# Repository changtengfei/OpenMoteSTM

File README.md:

View this project on [CADLAB.io](https://cadlab.io/project/1063). 

OpenSource Hardware of OpenMoteSTM
====================================================

Hello, here is the source of OpenMoteSTM board, including device library, schematic and PCB. All of those are designed by eagle. We also provide a 3d model for openmotestm using sketchUp!!! You can open the openmotestm.skp file with sketchUp to see what openmotestm looks like. Part of package/device/model came from the library of eagle and sparkfun. 

Using OpenMoteSTM with OpenWSN
====================================================

Hardware & Tools
----------------------------------------------------

* OpenMoteSTM Motes         Please Contact: tengfei.chang@gmail.com
* Micro-B USB Cables        You can buy them online anywhere, or maybe you already have one :)
* Jlink Debugger            https://www.segger.com/jlink-debug-probes.html
* Jlink adapter             https://www.segger.com/jlink-adapters-9pin-cortexm.html

Software Installation
----------------------------------------------------

* IAR Embedded Workbench for ARM : Version 6.60     http://www.iar.com
* python 2.7:               http://python.org/download/
* PySerial 2.6:             http://pyserial.sourceforge.net/
* PyDispatcher 2.0.3:       http://pydispatcher.sourceforge.net/
* PyWin32:                  https://sourceforge.net/projects/pywin32/files/pywin32/
* SCons:                    http://scons.org/download.php
* Tap for Windows:          http://openvpn.net/index.php/download/community-downloads.html
* Silicon Labs CP2102:      http://www.silabs.com/support/pages/document-library.aspx?p=Interface&f=USB%20Bridges&pn=CP2102

Installation of Tap
----------------------------------------------------
1. install tun
2. configure tun
    * Go: "Start"->"Programs"->Tap For Windows->utilities->"Add a new TAP virtual ethernet adapter" 
    * Open Network Adapter，Looking for "Local Area Connection" adapter which is created by Tap windows
    * Rename it by "OpenWSN"
    * Enter following code in a windows command prompt， setting IP：
    
            netsh interface ipv4 add address name=OpenWSN address=10.2.0.1 mask=255.255.0.0
            netsh interface ipv6 add address interface=OpenWSN address=bbbb::1/64   
    
    * Enable Routing ("IEEE802.3" is the network interface you are using to connect to internet)

            netsh interface ipv4 set interface interface=IEEE802.3 forwarding=enabled
            netsh interface ipv4 set interface interface=OpenWSN forwarding=enabled

            netsh interface ipv6 set interface interface=IEEE802.3 forwarding=enabled
            netsh interface ipv6 set interface interface=OpenWSN forwarding=enabled
    
    * Add path to routing table

            netsh interface ipv6 delete route bbbb::/64 OpenWSN
            netsh interface ipv6 add    route bbbb::/64 OpenWSN fe80::8

Source Code
-----------------------------------------------------
* openwsn-sw:               https://codeload.github.com/openwsn-berkeley/openwsn-sw/zip/REL-1.8.0
* openwsn-fw:               https://codeload.github.com/openwsn-berkeley/openwsn-fw/zip/REL-1.8.0
* coap:                     https://codeload.github.com/openwsn-berkeley/coap/zip/develop

-All extracted folders need to be place at same level-

Downloading led_blink Program
-----------------------------------------------------
1. Open "IAR for ARM"
2. GO: File->Open->Workspace
3. choosing "openmotestm.eww"
    * the file is at : openwsn-fw-REL-1.8.0\projects\openmotestm directory
4. All the projects will shown on the Workspace(left of the GUI)，right click to select "01bsp_leds-Debug" project, then choose "Set as Active" in the prompt menu.    
5. Downloading and Debugging by left clicking the "Green Triangle Button",
    * tips: "Ctrl + D" is the short-cut of this functions
6. After downloading，IAR will stop at debugging mode. Press F5 to start the program. You will see the LEDs will blink by sequence

Using OpenWSN Program
-----------------------------------------------------
1. Downloading "03oos_openwsn-Debug" program by the procedures above
2. Connect OpenMoteSTM to PC by USB Cabel，PC will install the Silicon driver for OpenMoteSTM
3. Open a windows prompt, and enter the following code to start openvisualizer
        cd "Your\openwsn-sw_REL-1.8.0\Directory"\software\openvisualizer\
        scons runweb
3. Open your favourite brower and type in "localhost:8080" or "127.0.0.1:8080", You will see the openwsn openvisualizer page.
4. click "toggle" button to set the mote as DAGROOT. If everything goes well, you will find the blue LED light and the green one blinks. To see what's going behind them, please visit: http://openwsn.org

Contact & Help
-----------------------------------------------------
If you have any questions, please don't hesitate to contact tengfei.chang@gmail.com

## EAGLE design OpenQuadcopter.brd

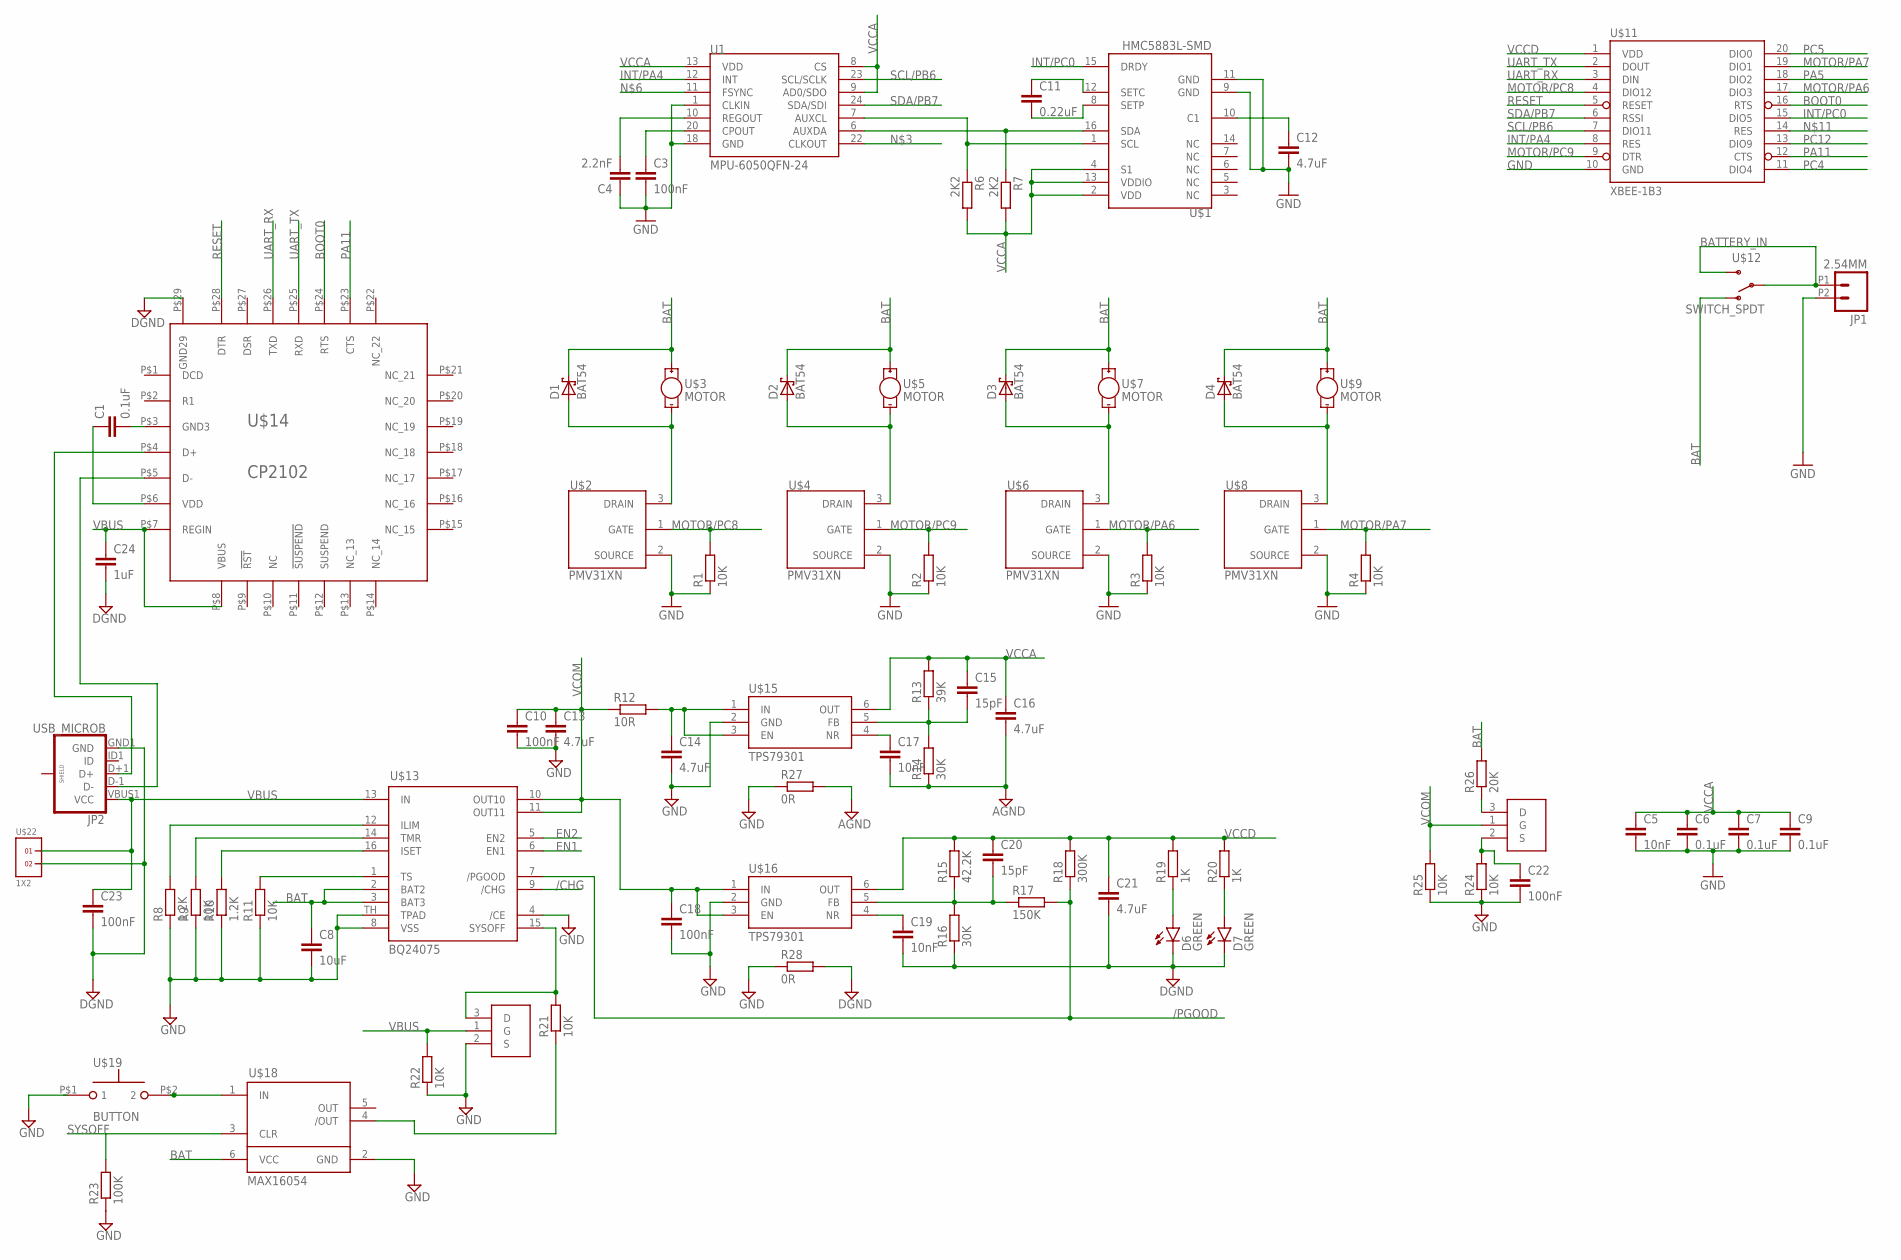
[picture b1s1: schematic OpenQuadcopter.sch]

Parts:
C1, C6, C7, C9: 0.1uF; C0402
C3, C10, C18, C22, C23: 100nF; C0402
C4: 2.2nF; C0402
C5, C17, C19: 10nF; C0402
C8: 10uF; C0603
C11: 0.22uF; C0402
C12, C13, C14, C16, C21: 4.7uF; C0603
C15, C20: 15pF; C0402
C24: 1uF; C0603
D1, D2, D3, D4: BAT54; SOT23
D6, D7: GREEN; LED-0603
JP1: 2.54MM; 1X02_2.54_SCREWTERM
JP2: USB_MICROB; USB-B-MICRO-SMD_V03
R1, R2, R3, R4, R9, R11, R21, R22, R24, R25: 10K; R0402
R6, R7: 2K2; R0402
R8, R10: 1.2K; R0402
R12: 10R; R0402
R13: 39K; R0402
R14, R16: 30K; R0402
R15: 42.2K; R0402
R17: 150K; R0402
R18: 300K; R0402
R19, R20: 1K; R0402
R23: 100K; R0402
R26: 20K; R0402
R27, R28: 0R; R0402
U1: MPU-6050QFN-24; QFN-24-TESTING
U$1: HMC5883L-SMD; 16LPCC
U$2, U$4, U$6, U$8: PMV31XN; SOT23-W
U$3, U$5, U$7, U$9: MOTOR; VIBE-MOTOR-10MM
U$11: XBEE-1B3; XBEE-SMD
U$12: SWITCH_SPDT; KPS-1290
U$13: BQ24075; QFN16
U$14: CP2102; QFN28-5X5
U$15, U$16: TPS79301; SOT23-6
U$17, U$20: 2N7002; SOT23-3
U$18: MAX16054; SOT23-6
U$19: BUTTON
U$22: 1X2

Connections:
/CHG: U$13.9 (/CHG)
/PGOOD: R17.2, R18.1, U$13.7 (/PGOOD)
AGND: C16.2, C17.2, R14.1, R27.2
BAT: C8.1, D1.3 (C), D2.3 (C), D3.3 (C), D4.3 (C), R26.2, U$3.+, U$5.+, U$7.+, U$9.+, U$12.O, U$13.2 (BAT2), U$13.3 (BAT3), U$18.6 (VCC)
BATTERY_IN: JP1.P1 (1), U$12.P, U$12.S
BOOT0: U$11.16 (RTS), U$14.P$24 (RTS)
DGND: C19.2, C21.2, C23.2, C24.2, D6.C, D7.C, JP2.GND1 (GND), R16.1, R28.2, U$14.P$29 (GND29), U$22.2
EN1: U$13.6 (EN1)
EN2: U$13.5 (EN2)
GND: C3.2, C4.1, C5.2, C6.2, C7.2, C8.2, C9.2, C10.2, C12.2, C13.2, C14.2, C18.2, C22.2, JP1.P2 (2), R1.1, R2.1, R3.1, R4.1, R8.1, R9.1, R10.1, R11.1, R22.1, R23.1, R24.1, R25.1, R27.1, R28.1, U1.1 (CLKIN), U1.18 (GND), U$1.9 (GND), U$1.11 (GND), U$2.2 (SOURCE), U$4.2 (SOURCE), U$6.2 (SOURCE), U$8.2 (SOURCE), U$11.10 (GND), U$13.4 (/CE), U$13.8 (VSS), U$13.TH (TPAD), U$15.2 (GND), U$16.2 (GND), U$17.2 (S), U$18.2 (GND)
INT/PA4: U1.12 (INT), U$11.8 (RES)
INT/PC0: U$1.15 (DRDY), U$11.15 (DIO5)
MOTOR/PA6: R3.2, U$6.1 (GATE), U$11.17 (DIO3)
MOTOR/PA7: R4.2, U$8.1 (GATE), U$11.19 (DIO1)
MOTOR/PC8: R1.2, U$2.1 (GATE), U$11.4 (DIO12)
MOTOR/PC9: R2.2, U$4.1 (GATE), U$11.9 (DTR)
unnamed: D2.1 (A), U$4.3 (DRAIN), U$5.-
unnamed: D1.1 (A), U$2.3 (DRAIN), U$3.-
unnamed: R6.1, U1.7 (AUXCL), U$1.1 (SCL)
unnamed: D3.1 (A), U$6.3 (DRAIN), U$7.-
unnamed: D4.1 (A), U$8.3 (DRAIN), U$9.-
unnamed: R7.1, U1.6 (AUXDA), U$1.16 (SDA)
unnamed: C4.2, U1.10 (REGOUT)
unnamed: C1.2, U$14.P$3 (GND3)
unnamed: C3.1, U1.20 (CPOUT)
unnamed: C11.1, U$1.12 (SETC)
unnamed: C11.2, U$1.8 (SETP)
unnamed: R21.1, U$18.4 (/OUT)
unnamed: C12.1, U$1.10 (C1)
unnamed: C1.1, U$14.P$6 (VDD)
unnamed: R8.2, U$13.12 (ILIM)
unnamed: R9.2, U$13.14 (TMR)
unnamed: R10.2, U$13.16 (ISET)
unnamed: R11.2, U$13.1 (TS)
unnamed: R21.2, U$13.15 (SYSOFF), U$17.3 (D)
unnamed: C14.1, R12.2, U$15.1 (IN), U$15.3 (EN)
unnamed: U$18.1 (IN), U$19.P$2 (2)
unnamed: C15.2, R13.1, R14.2, U$15.5 (FB)
unnamed: C17.1, U$15.4 (NR)
unnamed: C19.1, U$16.4 (NR)
unnamed: C20.2, R15.1, R16.2, R17.1, U$16.5 (FB)
unnamed: C22.1, R24.2, U$20.2 (S)
unnamed: D6.A, R19.1
unnamed: D7.A, R20.1
unnamed: R26.1, U$20.3 (D)
unnamed: JP2.D+1 (D+), U$14.P$4 (D+)
unnamed: JP2.D-1 (D-), U$14.P$5 (D-)
PA5: U$11.18 (DIO2)
PA11: U$11.12 (CTS), U$14.P$23 (CTS)
PC4: U$11.11 (DIO4)
PC5: U$11.20 (DIO0)
PC12: U$11.13 (DIO9)
RESET: U$11.5 (RESET), U$14.P$28 (DTR)
SCL/PB6: U1.23 (SCL/SCLK), U$11.7 (DIO11)
SDA/PB7: U1.24 (SDA/SDI), U$11.6 (RSSI)
SYSOFF: R23.2, U$18.3 (CLR)
UART_RX: U$11.3 (DIN), U$14.P$26 (TXD)
UART_TX: U$11.2 (DOUT), U$14.P$25 (RXD)
VBUS: C23.1, C24.1, JP2.VBUS1 (VCC), R22.2, U$13.13 (IN), U$14.P$7 (REGIN), U$14.P$8 (VBUS), U$17.1 (G), U$22.1
VCCA: C5.1, C6.1, C7.1, C9.1, C15.1, C16.1, R6.2, R7.2, R13.2, U1.8 (CS), U1.9 (AD0/SDO), U1.13 (VDD), U$1.2 (VDD), U$1.4 (S1), U$1.13 (VDDIO), U$15.6 (OUT)
VCCD: C20.1, C21.1, R15.2, R18.2, R19.2, R20.2, U$11.1 (VDD), U$16.6 (OUT)
VCOM: C10.1, C13.1, C18.1, R12.1, R25.2, U$13.10 (OUT10), U$13.11 (OUT11), U$16.1 (IN), U$16.3 (EN), U$20.1 (G)

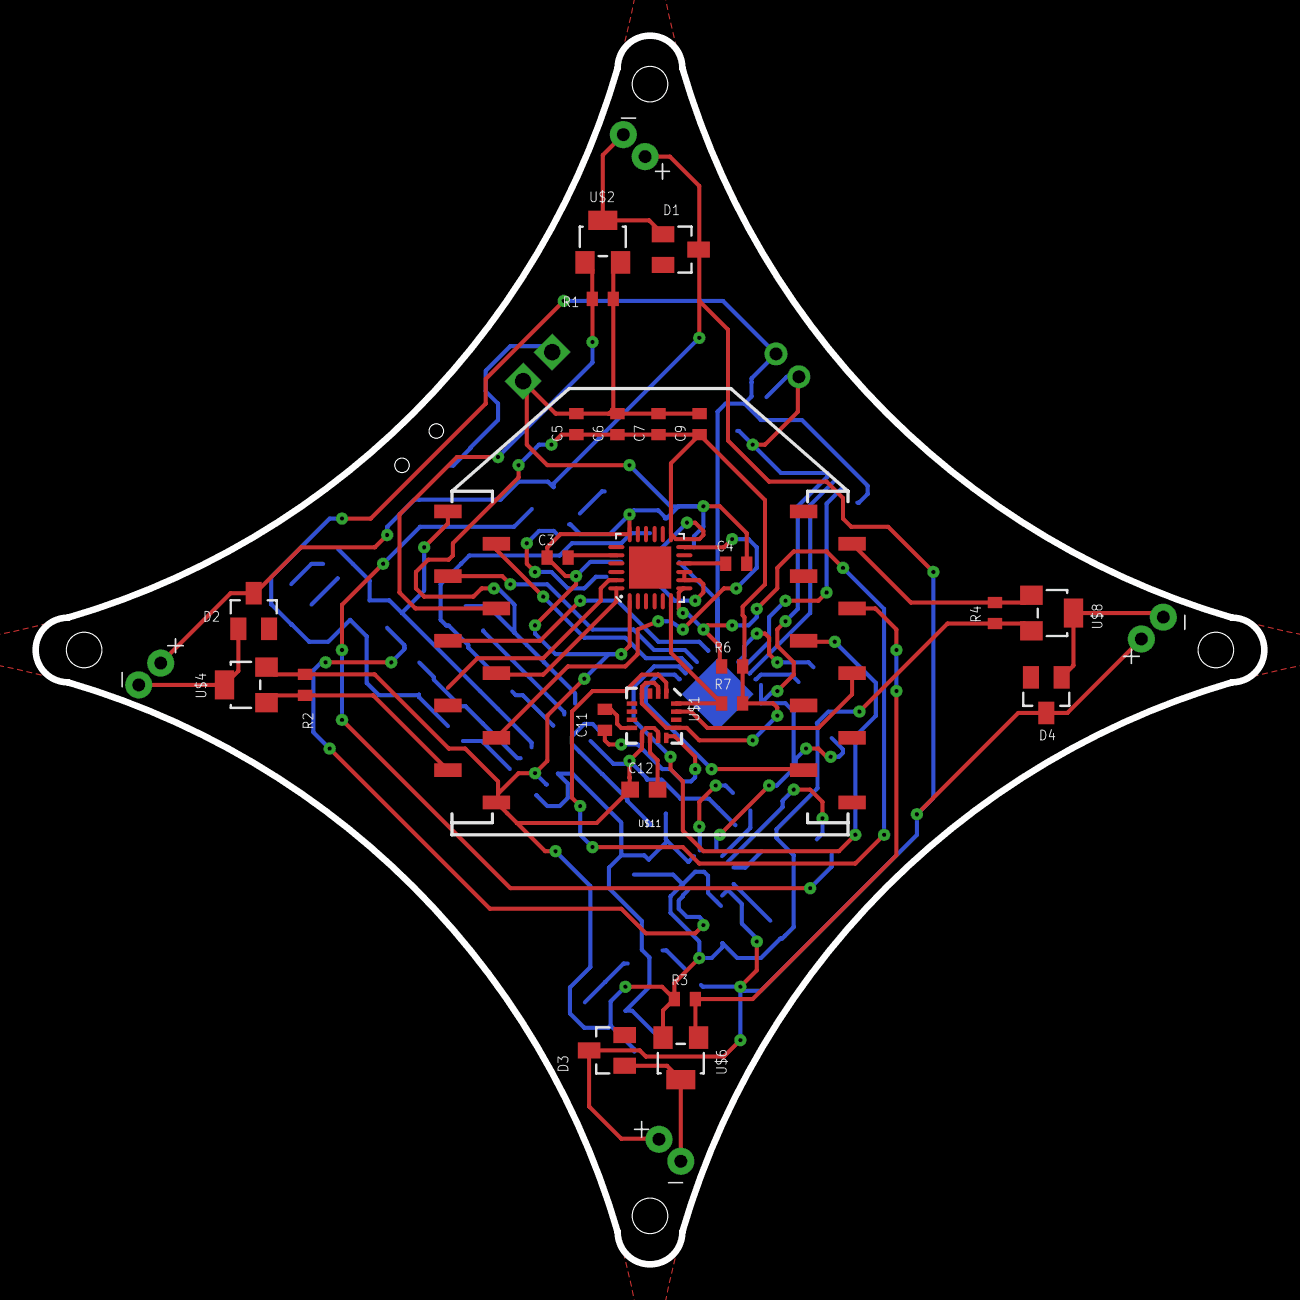
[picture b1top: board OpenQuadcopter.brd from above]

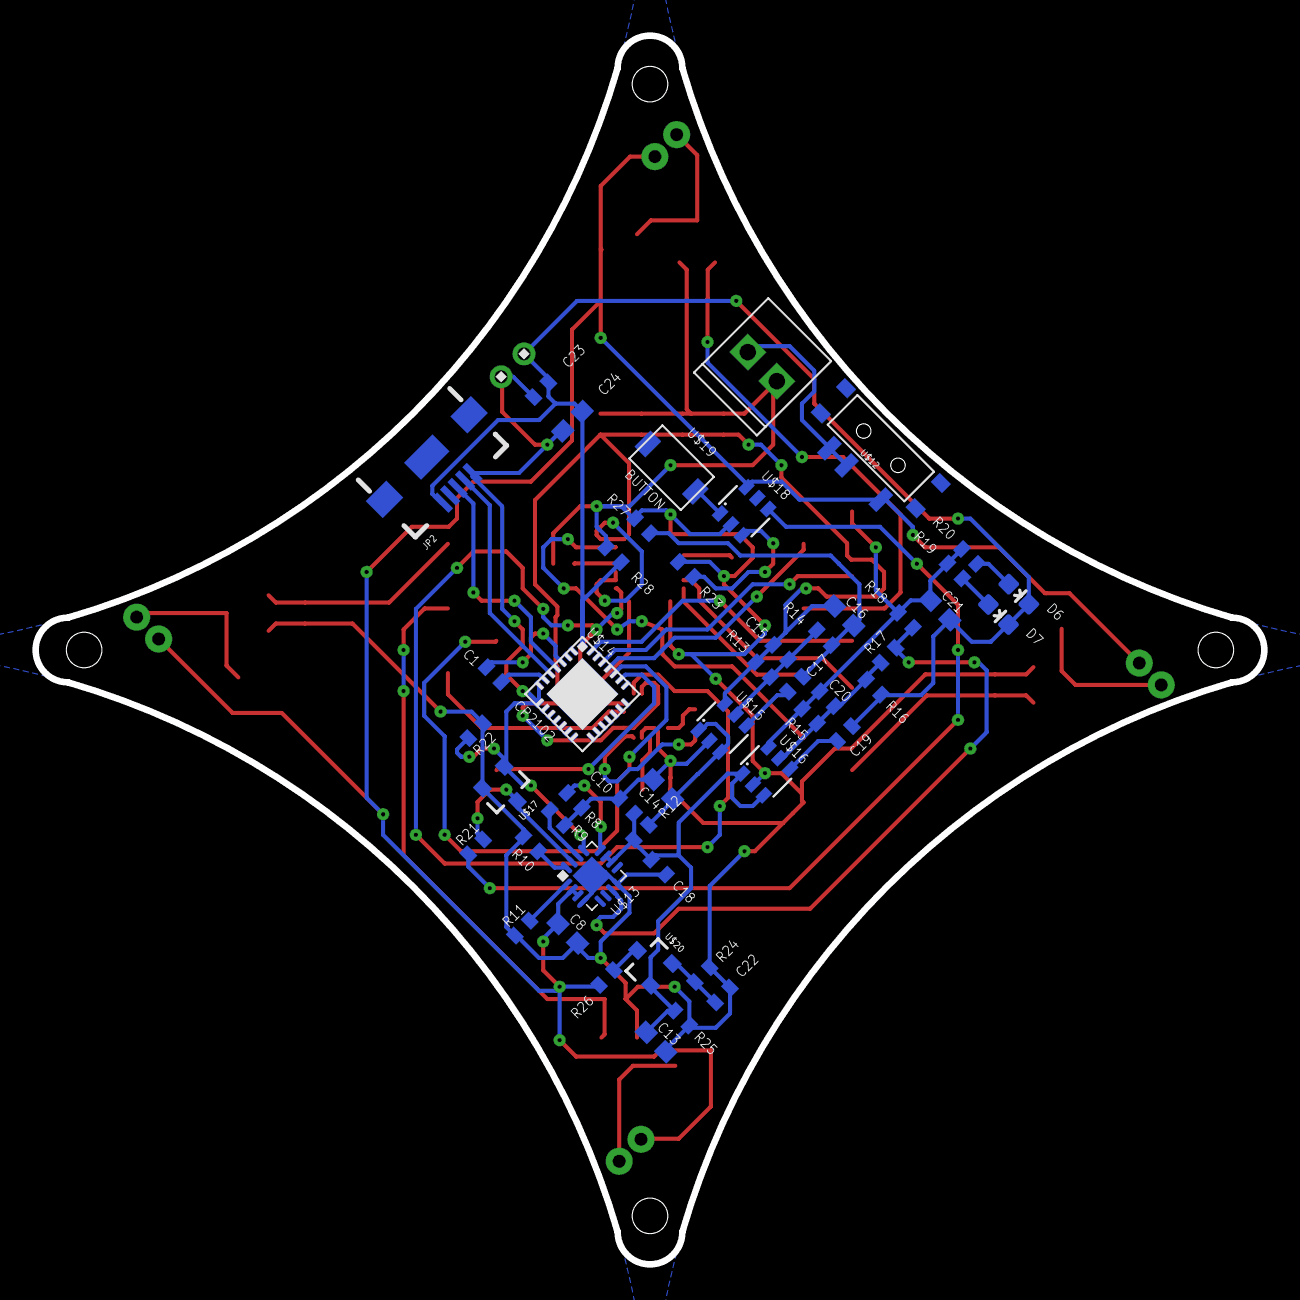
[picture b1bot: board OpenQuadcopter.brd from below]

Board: 2 copper layers, 76.0 x 76.0 mm, 79 parts (50 on the bottom side), 55 nets.

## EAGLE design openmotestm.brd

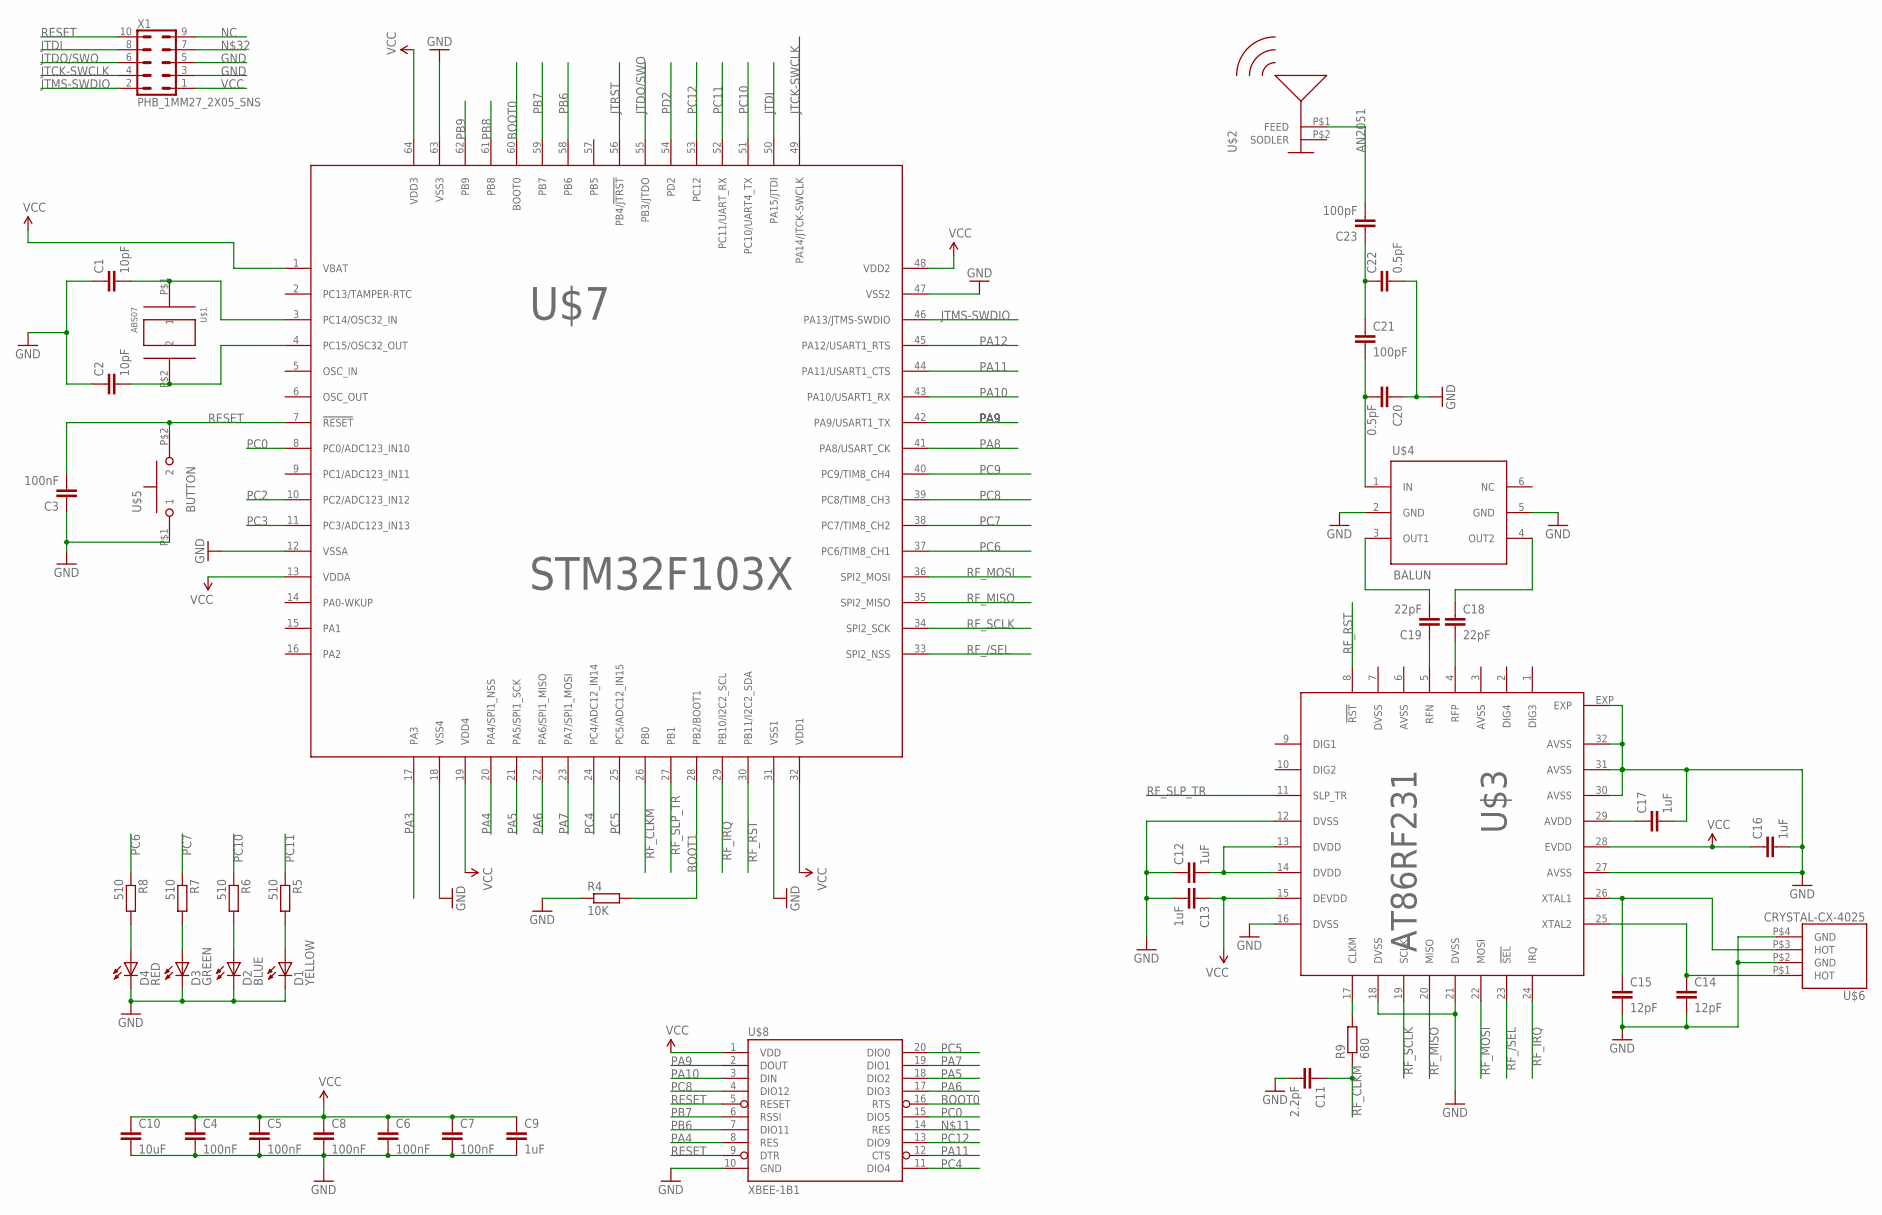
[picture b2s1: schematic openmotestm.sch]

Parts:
C1, C2: 10pF; C0402
C3, C4, C5, C6, C7, C8: 100nF; C0402
C9, C12, C13, C16, C17: 1uF; C0603
C10: 10uF; C0603
C11: 2.2pF; C0402
C14, C15: 12pF; C0402
C18, C19: 22pF; C0402
C20, C22: 0.5pF; C0402
C21, C23: 100pF; C0402
D1: YELLOW; LED-0603
D2: BLUE; LED-0603
D3: GREEN; LED-0603
D4: RED; LED-0603
R4: 10K; R0402
R5, R6, R7, R8: 510; R0402
R9: 680; R0402
U$1: ABS07
U$2: AN2051
U$3: AT86RF231; QFN32
U$4: BALUN
U$5: BUTTON
U$6: CRYSTAL-CX-4025; CX-4025
U$7: STM32F103X; LQFP-ST-64-2
U$8: XBEE-1B1; XBEE-1
X1: PHB_1MM27_2X05_SNS

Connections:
BOOT0: U$7.60 (BOOT0), U$8.16 (RTS)
BOOT1: R4.2, U$7.28 (PB2/BOOT1)
GND: C1.1, C2.1, C3.1, C4.2, C5.2, C6.2, C7.2, C8.2, C9.2, C10.2, C11.2, C12.1, C13.2, C14.2, C15.2, C16.2, C17.2, C20.1, C22.2, D1.C, D2.C, D3.C, D4.C, R4.1, U$3.12 (DVSS), U$3.16 (DVSS), U$3.18 (DVSS), U$3.21 (DVSS), U$3.27 (AVSS), U$3.30 (AVSS), U$3.31 (AVSS), U$3.32 (AVSS), U$3.EXP, U$4.2 (GND), U$4.5 (GND), U$5.P$1 (1), U$6.P$2 (GND), U$6.P$4 (GND), U$7.12 (VSSA), U$7.18 (VSS4), U$7.31 (VSS1), U$7.47 (VSS2), U$7.63 (VSS3), U$8.10 (GND), X1.3, X1.5
JTCK-SWCLK: U$7.49 (PA14/JTCK-SWCLK), X1.4
JTDI: U$7.50 (PA15/JTDI), X1.8
JTDO/SWO: U$7.55 (PB3/JTDO), X1.6
JTMS-SWDIO: U$7.46 (PA13/JTMS-SWDIO), X1.2
JTRST: U$7.56 (PB4/!JTRST)
unnamed: C1.2, U$1.P$1 (1), U$7.3 (PC14/OSC32_IN)
unnamed: C2.2, U$1.P$2 (2), U$7.4 (PC15/OSC32_OUT)
unnamed: R9.2, U$3.17 (CLKM)
unnamed: C14.1, U$3.25 (XTAL2), U$6.P$1 (HOT)
unnamed: D1.A, R5.2
unnamed: D2.A, R6.2
unnamed: D3.A, R7.2
unnamed: D4.A, R8.2
unnamed: C15.1, U$3.26 (XTAL1), U$6.P$3 (HOT)
unnamed: C12.2, U$3.13 (DVDD), U$3.14 (DVDD)
unnamed: C18.2, U$3.4 (RFP)
unnamed: C19.1, U$3.5 (RFN)
unnamed: C19.2, U$4.3 (OUT1)
unnamed: C17.1, U$3.29 (AVDD)
unnamed: C18.1, U$4.4 (OUT2)
unnamed: C20.2, C21.2, U$4.1 (IN)
unnamed: C21.1, C22.1, C23.1
unnamed: C23.2, U$2.P$1 (FEED)
NC: X1.9
PA3: U$7.17 (PA3)
PA4: U$7.20 (PA4/SPI1_NSS), U$8.8 (RES)
PA5: U$7.21 (PA5/SPI1_SCK), U$8.18 (DIO2)
PA6: U$7.22 (PA6/SPI1_MISO), U$8.17 (DIO3)
PA7: U$7.23 (PA7/SPI1_MOSI), U$8.19 (DIO1)
PA8: U$7.41 (PA8/USART_CK)
PA9: U$7.42 (PA9/USART1_TX), U$8.2 (DOUT)
PA10: U$7.43 (PA10/USART1_RX), U$8.3 (DIN)
PA11: U$7.44 (PA11/USART1_CTS), U$8.12 (CTS)
PA12: U$7.45 (PA12/USART1_RTS)
PB6: U$7.58 (PB6), U$8.7 (DIO11)
PB7: U$7.59 (PB7), U$8.6 (RSSI)
PB8: U$7.61 (PB8)
PB9: U$7.62 (PB9)
PC0: U$7.8 (PC0/ADC123_IN10), U$8.15 (DIO5)
PC2: U$7.10 (PC2/ADC123_IN12)
PC3: U$7.11 (PC3/ADC123_IN13)
PC4: U$7.24 (PC4/ADC12_IN14), U$8.11 (DIO4)
PC5: U$7.25 (PC5/ADC12_IN15), U$8.20 (DIO0)
PC6: R8.1, U$7.37 (PC6/TIM8_CH1)
PC7: R7.1, U$7.38 (PC7/TIM8_CH2)
PC8: U$7.39 (PC8/TIM8_CH3), U$8.4 (DIO12)
PC9: U$7.40 (PC9/TIM8_CH4)
PC10: R6.1, U$7.51 (PC10/UART4_TX)
PC11: R5.1, U$7.52 (PC11/UART_RX)
PC12: U$7.53 (PC12), U$8.13 (DIO9)
PD2: U$7.54 (PD2)
RESET: C3.2, U$5.P$2 (2), U$7.7 (!RESET), U$8.5 (RESET), U$8.9 (DTR), X1.10
RF_/SEL: U$3.23 (!SEL), U$7.33 (SPI2_NSS)
RF_CLKM: C11.1, R9.1, U$7.26 (PB0)
RF_IRQ: U$3.24 (IRQ), U$7.29 (PB10/I2C2_SCL)
RF_MISO: U$3.20 (MISO), U$7.35 (SPI2_MISO)
RF_MOSI: U$3.22 (MOSI), U$7.36 (SPI2_MOSI)
RF_RST: U$3.8 (!RST), U$7.30 (PB11/I2C2_SDA)
RF_SCLK: U$3.19 (SCLK), U$7.34 (SPI2_SCK)
RF_SLP_TR: U$3.11 (SLP_TR), U$7.27 (PB1)
VCC: C4.1, C5.1, C6.1, C7.1, C8.1, C9.1, C10.1, C13.1, C16.1, U$3.15 (DEVDD), U$3.28 (EVDD), U$7.1 (VBAT), U$7.13 (VDDA), U$7.19 (VDD4), U$7.32 (VDD1), U$7.48 (VDD2), U$7.64 (VDD3), U$8.1 (VDD), X1.1

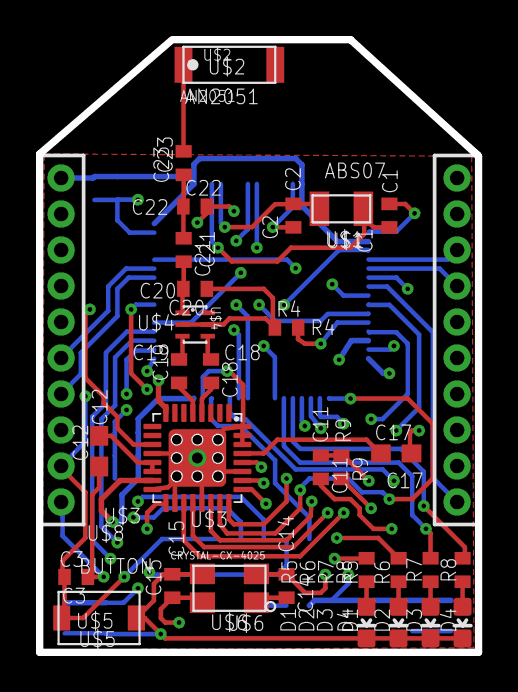
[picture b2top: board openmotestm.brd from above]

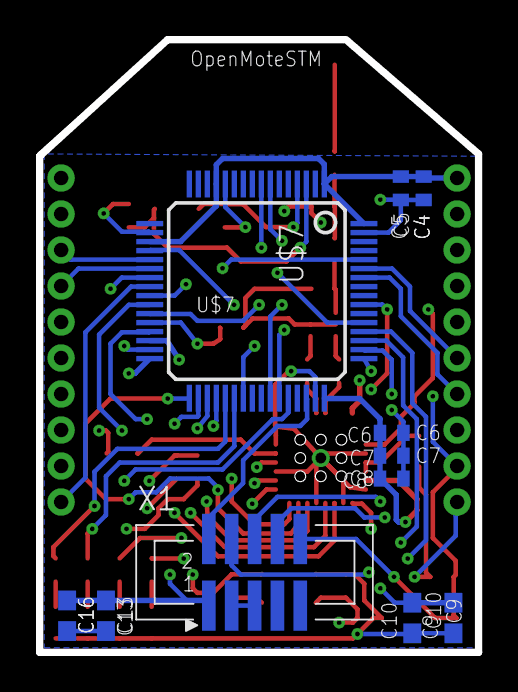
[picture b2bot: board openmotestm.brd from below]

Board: 4 copper layers, 24.4 x 34.0 mm, 42 parts (11 on the bottom side), 53 nets.

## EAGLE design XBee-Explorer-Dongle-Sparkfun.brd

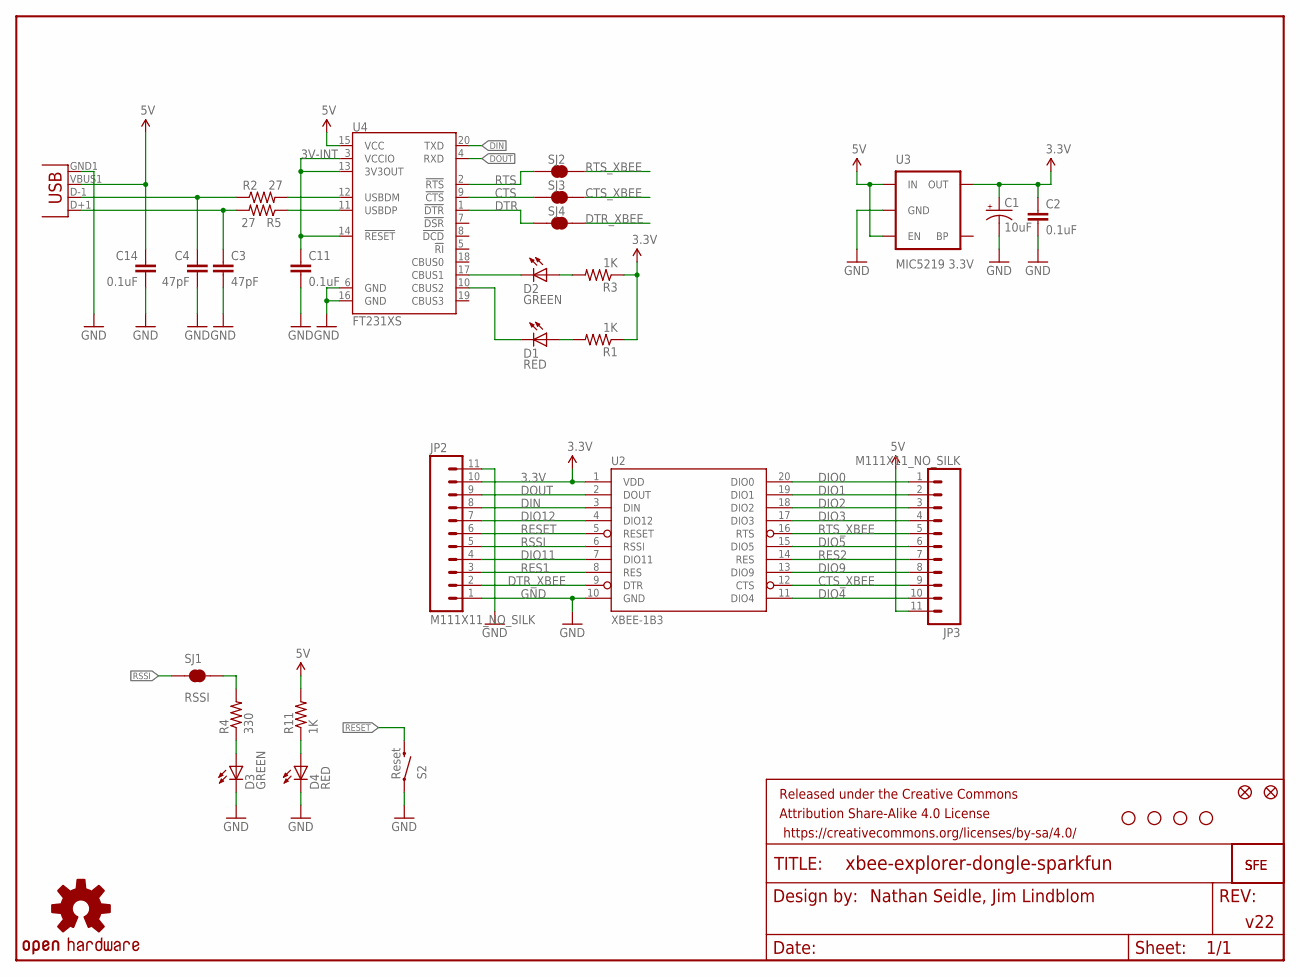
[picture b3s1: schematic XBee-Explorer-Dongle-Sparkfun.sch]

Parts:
C1: 10uF; EIA3216
C2, C11, C14: 0.1uF; 0603-CAP
C3, C4: 47pF; 0603-CAP
D1, D4: RED; LED-0603
D2, D3: GREEN; LED-0603
FID1, FID2: FIDUCIAL1X2; FIDUCIAL-1X2
FRAME1: FRAME-LETTER; CREATIVE_COMMONS
JP1: USBA-SMD-MALE-LOCKING; USB-A-SMT-MALE-LOCKING
JP2, JP3: M111X11_NO_SILK; 1X11_NO_SILK
R1, R3, R11: 1K; 0603-RES
R2, R5: 27; 0603-RES
R4: 330; 0603-RES
S2: Reset; TACTILE_SWITCH_SMD
SJ1, SJ2, SJ3, SJ4: RSSI; SJ_2S-TRACE
U2: XBEE-1B3; XBEE-SMD
U3: MIC5219 3.3V; SOT23-5
U4: FT231XS; SSOP20_L
U$1: LOGO-SFESK; SFE-LOGO-FLAME
U$4: LOGO-SFENEW; SFE-NEW-WEBLOGO
U$5, U$9, U$10, U$11: STAND-OFF
U$7: OSHW-LOGOS; OSHW-LOGO-S

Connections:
3.3V: C1.A (+), C2.1, JP2.10, R1.1, R3.1, U2.1 (VDD), U3.5 (OUT)
3V-INT: C11.1, U4.3 (VCCIO), U4.13 (3V3OUT), U4.14 (!RESET)
5V: C14.1, JP1.VBUS1 (VBUS), JP3.11, R11.2, U3.1 (IN), U3.3 (EN), U4.15 (VCC)
CTS: SJ3.1, U4.9 (!CTS)
CTS_XBEE: JP3.9, SJ3.2, U2.12 (CTS)
DIN: JP2.8, U2.3 (DIN), U4.20 (TXD)
DIO0: JP3.1, U2.20 (DIO0)
DIO1: JP3.2, U2.19 (DIO1)
DIO2: JP3.3, U2.18 (DIO2)
DIO3: JP3.4, U2.17 (DIO3)
DIO4: JP3.10, U2.11 (DIO4)
DIO5: JP3.6, U2.15 (DIO5)
DIO9: JP3.8, U2.13 (DIO9)
DIO11: JP2.4, U2.7 (DIO11)
DIO12: JP2.7, U2.4 (DIO12)
DOUT: JP2.9, U2.2 (DOUT), U4.4 (RXD)
DTR: SJ4.1, U4.1 (!DTR)
DTR_XBEE: JP2.2, SJ4.2, U2.9 (DTR)
GND: C1.C (-), C2.2, C3.2, C4.2, C11.2, C14.2, D3.C, D4.C, JP1.GND1 (GND), JP2.1, JP2.11, S2.1, U2.10 (GND), U3.2 (GND), U4.6 (GND), U4.16 (GND)
unnamed: D1.A, R1.2
unnamed: D3.A, R4.1
unnamed: C4.1, JP1.D-1 (D-), R2.1
unnamed: D2.A, R3.2
unnamed: R2.2, U4.12 (USBDM)
unnamed: C3.1, JP1.D+1 (D+), R5.2
unnamed: R5.1, U4.11 (USBDP)
unnamed: R4.2, SJ1.2
unnamed: D4.A, R11.1
RES1: JP2.3, U2.8 (RES)
RES2: JP3.7, U2.14 (RES)
RESET: JP2.6, S2.3 (2), U2.5 (RESET)
RSSI: JP2.5, SJ1.1, U2.6 (RSSI)
RTS: SJ2.1, U4.2 (!RTS)
RTS_XBEE: JP3.5, SJ2.2, U2.16 (RTS)
RXLED: D2.C, U4.17 (CBUS1)
TXLED: D1.C, U4.10 (CBUS2)

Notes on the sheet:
Nathan Seidle, Jim Lindblom
v22

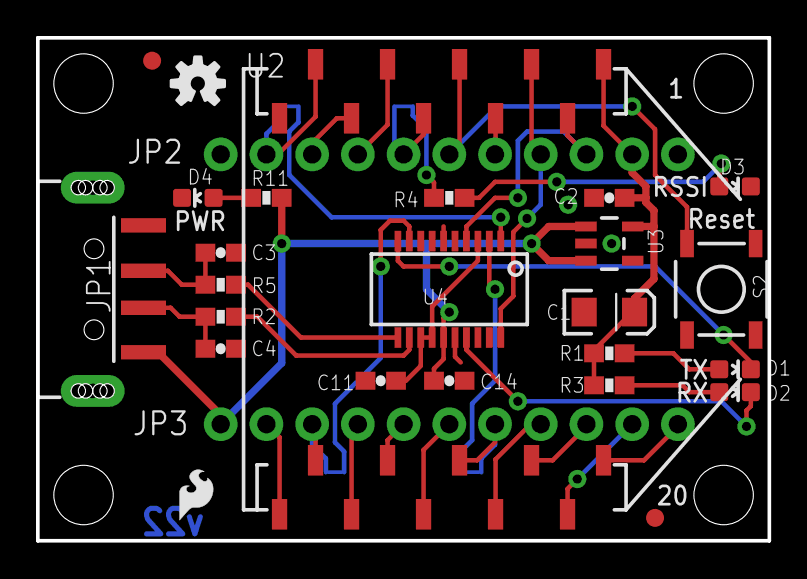
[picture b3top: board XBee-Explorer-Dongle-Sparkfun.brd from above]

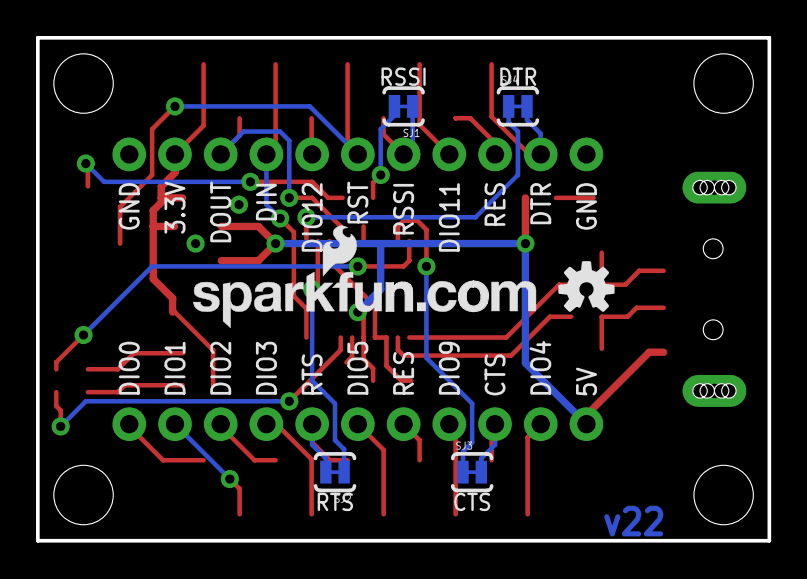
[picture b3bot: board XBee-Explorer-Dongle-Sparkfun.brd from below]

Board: 2 copper layers, 40.6 x 27.9 mm, 38 parts (6 on the bottom side), 36 nets.

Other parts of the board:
U$8: OSHW-LOGOS; OSHW-LOGO-S

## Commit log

2014-07-26 MASTER. Add documents and library
2014-07-26 MASTER. Update README.
2014-07-28 Update library and schematic.
2014-07-29 add sch and brd
2014-07-29 finish the board
2014-07-30 fix.
2014-07-31 right position in brd.
2014-07-31 add skp 3d model file for openmotestm.
2014-08-04 update sketchup model
2014-08-07 Add a picture for quadcopter
2014-08-07 change the footprint of capacity larger than 1uF to 0603 footprint. Update 3D sketchUp model
2014-08-08 add xbee battery board, openquadcopter's schematic and pcb file.
2014-08-09 wrap up openquadcopter board.
2014-08-11 Change the PWM's TIM. (Do not use TIM1 for pwm, since the pins are also related to SPI pins)
2014-08-11 Add holes as a pendant.
2014-08-12 update openquadcopter.
2014-08-15 change the pcb to satisfy minimum clearance of 5 mil
2014-08-15 add some stuff.
2014-08-16 update openmotestm
2014-08-17 drawing quadcopter
2014-08-18 Amazing testbed - "The shelf", had been added.
2014-08-18 fix testbed-MICL
2014-08-19 change the color of the shelf
2014-09-09 redesign the plank.
2014-10-15 Add XBee-Explorer-Dongle-Sparkfun. Update openmotestm. arrange the layout of openquadcopter board.
2014-10-16 smooth the corner of quadcopter.
2014-10-17 add Gerber files.
2014-10-20 add bom file.
2014-10-23 remove unused route
2014-10-27 exchange the top layer and bottom layer.
2014-10-28 recover BOM.
2014-11-28 Fix the package of chips.
2014-12-02 Fix the package of crystal-CX4025
2014-12-02 Revert "Fix the package of crystal-CX4025"
    This reverts commit 4aa64b79fca5c8ea969664931983d918d7a77836.
2014-12-03 remove taps.
2014-12-03 Fix place Layer.
2014-12-03 update gerber files
2014-12-19 Publish openquadcopter extention board.
2014-12-22 Fixed.
2014-12-23 update the stop and cream layer for QFN32 package.
2014-12-23 update QFN packet to sch and brd files.
2015-04-06 update PB6
2015-09-11 Correct the name PMV31XN.
2016-02-26 add 0.1uF capacitor between VDD and GND pin of CP2102.
2018-05-19 Backlink to CADLAB.io has been added.

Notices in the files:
parts and their libraries:
SparkFun-Connectors: Licensing: Creative Commons ShareAlike 4.0 International - https://creativecommons.org/licenses/by-sa/4.0
SparkFun-Connectors: Licensing: CC v3.0 Share-Alike You are welcome to use this library for commercial purposes.
SparkFun-Aesthetics: Released under the Creative Commons
